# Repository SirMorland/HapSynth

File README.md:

# HapSynth

An 8-voice digital substractive synthesizer with motorized slider for haptic feedback.

## Demo

[https://www.youtube.com/watch?v=hl_LQ_ap-Gw](https://www.youtube.com/watch?v=hl_LQ_ap-Gw)

## Schematics

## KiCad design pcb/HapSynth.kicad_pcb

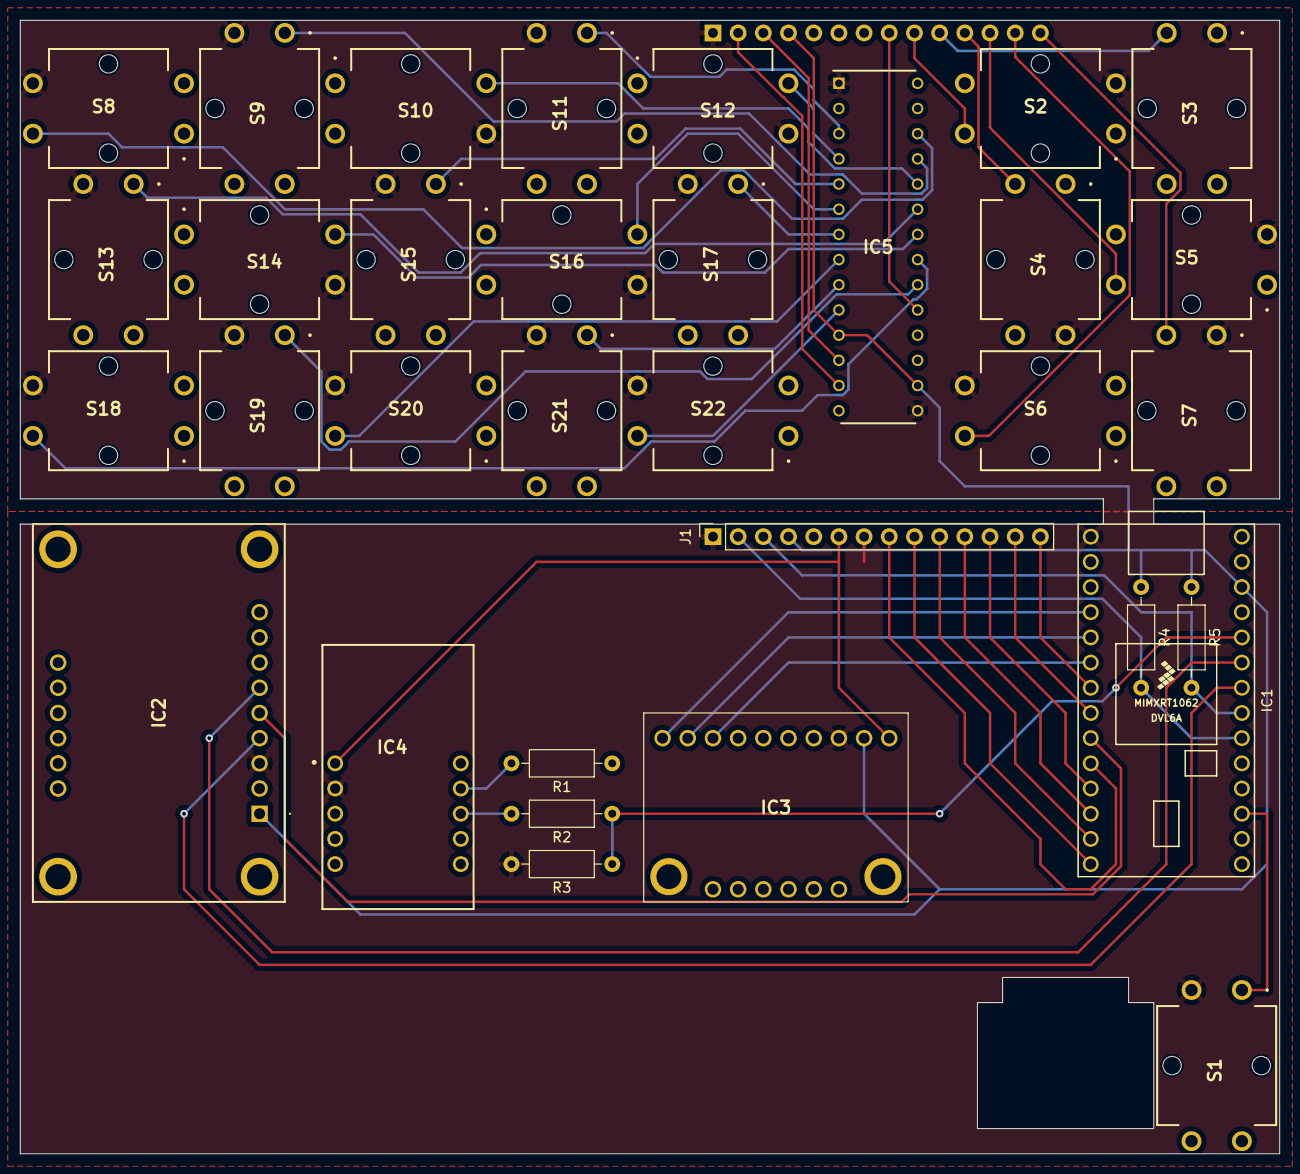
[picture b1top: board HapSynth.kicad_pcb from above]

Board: 2 copper layers, 127.0 x 114.3 mm, 34 parts (1 on the bottom side), 46 nets.

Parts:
IC1: 4323; Teensy40-simple
IC2: 3678
IC3: 2448
IC4: 1501
IC5: MCP23018-E_SP; DIP794W56P254L3486H508Q28N
J1: Conn_01x14_Socket; PinSocket_1x14_P2.54mm_Vertical
J2: Conn_01x14_Pin; PinSocket_1x14_P2.54mm_Vertical
R1: 1M; R_Axial_DIN0207_L6.3mm_D2.5mm_P10.16mm_Horizontal
R2, R4, R5: 1K; R_Axial_DIN0207_L6.3mm_D2.5mm_P10.16mm_Horizontal
R3: 1.5K; R_Axial_DIN0207_L6.3mm_D2.5mm_P10.16mm_Horizontal
S1, S2, S3, S4, S5, S6, S7, S8, S9, S10, S11, S12, S13, S14, S15, S16, S17, S18, S19, S20, S21, S22: B3F-4055; B3F-4055-bent

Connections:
+BATT: IC3.1 (VM), IC4.1 (BAT+), J1.6
/Sheetname: User Interface/BTN1: J2.9, S2.2
/Sheetname: User Interface/BTN2: J2.10, S3.3
/Sheetname: User Interface/BTN3: J2.11, S4.3
/Sheetname: User Interface/BTN4: J2.12, S5.2
/Sheetname: User Interface/BTN5: J2.13, S6.2
/Sheetname: User Interface/BTN6: J2.14, S7.3
/Sheetname: User Interface/INT: IC5.19 (INTA), J2.8
/Sheetname: User Interface/SCL: IC5.12 (SCL), J2.3
/Sheetname: User Interface/SDA: IC5.13 (SDA), J2.2
GND: IC1.1 (GND), IC2.3 (GND), IC3.3 (GND_1), IC4.2 (GND), IC5.1 (VSS), IC5.15 (ADDR), J1.1, J1.7, J2.1, R3.2, S1.3, S2.3, S3.1, S4.2, S5.3, S6.4, S7.1, S8.4, S9.3, S10.4, S11.3, S12.4, S13.3, S14.4, S15.3, S16.4, S17.3, S18.4, S19.3, S20.4, S21.3, S22.4
unnamed: IC1.4 (2_OUT2), IC3.10 (PWMA)
unnamed: IC1.5 (3_LRCLK2), IC3.9 (AIN2)
unnamed: IC1.6 (4_BCLK2), IC3.8 (AIN1)
unnamed: IC1.7 (5_IN2), J1.14
unnamed: IC1.8 (6_OUT1D), J1.13
unnamed: IC1.9 (7_RX2_OUT1A), IC2.5 (DIN)
unnamed: IC1.10 (8_TX2_IN1), J1.8
unnamed: IC1.11 (9_OUT1C), J1.12
unnamed: IC1.12 (10_CS_MQSR), J1.11
unnamed: IC1.13 (11_MOSI_CTX1), J1.10
unnamed: IC1.14 (12_MISO_MQSL), J1.9
unnamed: IC1.22 (15_A1_RX3_SPDIF_IN), S1.1
unnamed: IC1.25 (18_A4_SDA0), J1.2, R4.2
unnamed: IC1.26 (19_A5_SCL0), J1.3, R5.2
unnamed: IC1.27 (20_A6_TX5_LRCLK1), IC2.4 (WSEL)
unnamed: IC1.28 (21_A7_RX5_BCLK1), IC2.6 (BCLK)
unnamed: IC1.29 (22_A8_CTX1), R2.1, R3.1
unnamed: IC4.8 (#1), R2.2
unnamed: IC4.9 ('0), R1.2
unnamed: IC5.20 (GPA0), S19.1
unnamed: IC5.21 (GPA1), S18.2
unnamed: IC5.22 (GPA2), S14.2
unnamed: IC5.23 (GPA3), S13.1
unnamed: IC5.24 (GPA4), S10.2
unnamed: IC5.25 (GPA5), S9.1
unnamed: IC5.26 (GPA6), S8.2
unnamed: IC5.3 (GPB0), S11.1
unnamed: IC5.4 (GPB1), S12.2
unnamed: IC5.5 (GPB2), S15.1
unnamed: IC5.6 (GPB3), S16.2
unnamed: IC5.7 (GPB4), S17.1
unnamed: IC5.8 (GPB5), S20.2
unnamed: IC5.9 (GPB6), S21.1
unnamed: IC5.10 (GPB7), S22.2
VCC: IC1.31 (3V3), IC2.1 (VIN), IC3.2 (VCC), IC5.11 (VDD), IC5.16 (~RESET), J1.4, J2.4, R4.1, R5.1

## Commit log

2023-05-12 feat: Initial commit
2023-05-12 Create LICENSE
2023-05-12 feat: Reorder repo
2023-05-12 feat: Add KiCad files
2023-05-12 feat: Add README
2023-05-12 feat: Add case 3D-model
2023-05-12 feat: Add schematics to README

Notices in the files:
pcb/HapSynth.kicad_pcb:
Licence: MIT
